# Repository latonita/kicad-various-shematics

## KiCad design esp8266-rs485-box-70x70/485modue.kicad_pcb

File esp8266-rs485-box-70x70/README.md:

esp8266 + rs485 module in 70x70mm box

made to read data from power meter with 485 interface

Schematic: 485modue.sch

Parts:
C1, C4: 0.1uF; C_0805_2012Metric
C2: 0.01uF; C_0603_1608Metric
C3: 470uF; CP_Radial_D8.0mm_P3.80mm
D1: LED; LED_D3.0mm
F1: 250mA; R_Axial_Power_L25.0mm_W9.0mm_P27.94mm
J1: 220AC; TerminalBlock_Altech_AK300-2_P5.00mm
J2: Conn_01x06_Male; PinHeader_1x06_P2.54mm_Vertical
J3: RS485; TerminalBlock_Altech_AK300-2_P5.00mm
R1, R2, R4, R9: 10k; R_0805_2012Metric
R3: 5.7k; R_0805_2012Metric
R5: 680; R_0805_2012Metric
R6, R8: 560; R_0805_2012Metric
R7: 120; R_0805_2012Metric
RV1: S14K385; RV_Disc_D12mm_W7.5mm_P7.5mm
SW1: Reset; SW_Tactile_SPST_Angled_PTS645Vx39-2LFS
U1: HLK-PM03; Converter_ACDC_HLK-PM01_THT
U2: ESP-12E; RF_Module_ESP-12E_SMD
U3: MAX3485; SOIC-8_3.9x4.9mm_P1.27mm

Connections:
+3V3: C1.1, C2.1, C3.1, C4.2, J2.6, R1.1, R2.1, R4.1, R8.2, R9.1, U1.4, U2.8, U3.8 (VCC)
/A: J3.1, R7.2, R8.1, U3.6 (A)
/AC_L: F1.1, RV1.1, U1.1
/AC_N: J1.1, RV1.2, U1.2
/B: J3.2, R6.2, R7.1, U3.7 (B)
/DE: R3.1, U2.16, U3.2 (~RE), U3.3 (DE)
/DI: U2.19, U3.4 (DI)
/FLASH: J2.5, R4.2, U2.18
/L: F1.2, J1.2
/RO: R9.2, U2.20, U3.1 (RO)
/RX: J2.2, U2.21
/TX: J2.1, U2.22
GND: C1.2, C2.2, C3.2, C4.1, D1.1, J2.3, J2.4, R3.2, R6.1, SW1.1, U1.3, U2.15, U3.5 (GND)
unnamed: D1.2, R5.1
unnamed: R1.2, U2.3
unnamed: R2.2, SW1.2, U2.1
unnamed: R5.2, U2.7

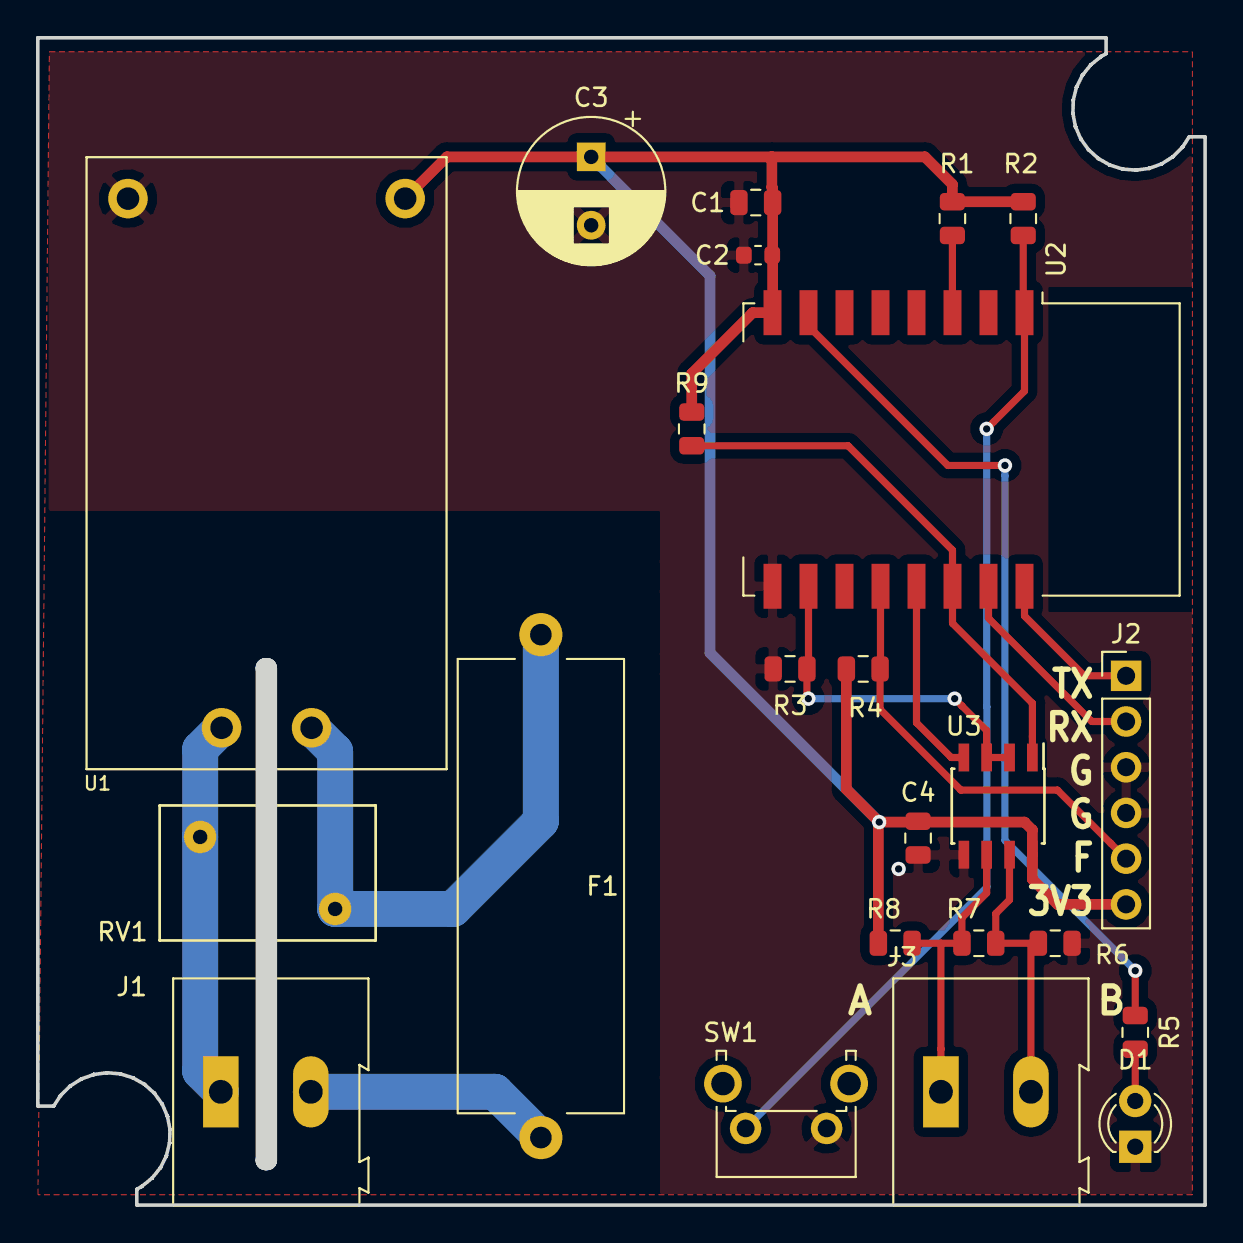
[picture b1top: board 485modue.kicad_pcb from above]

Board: 2 copper layers, 64.8 x 64.8 mm, 23 parts (0 on the bottom side), 17 nets.

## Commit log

2018-11-27 box70x70 + 485 module
